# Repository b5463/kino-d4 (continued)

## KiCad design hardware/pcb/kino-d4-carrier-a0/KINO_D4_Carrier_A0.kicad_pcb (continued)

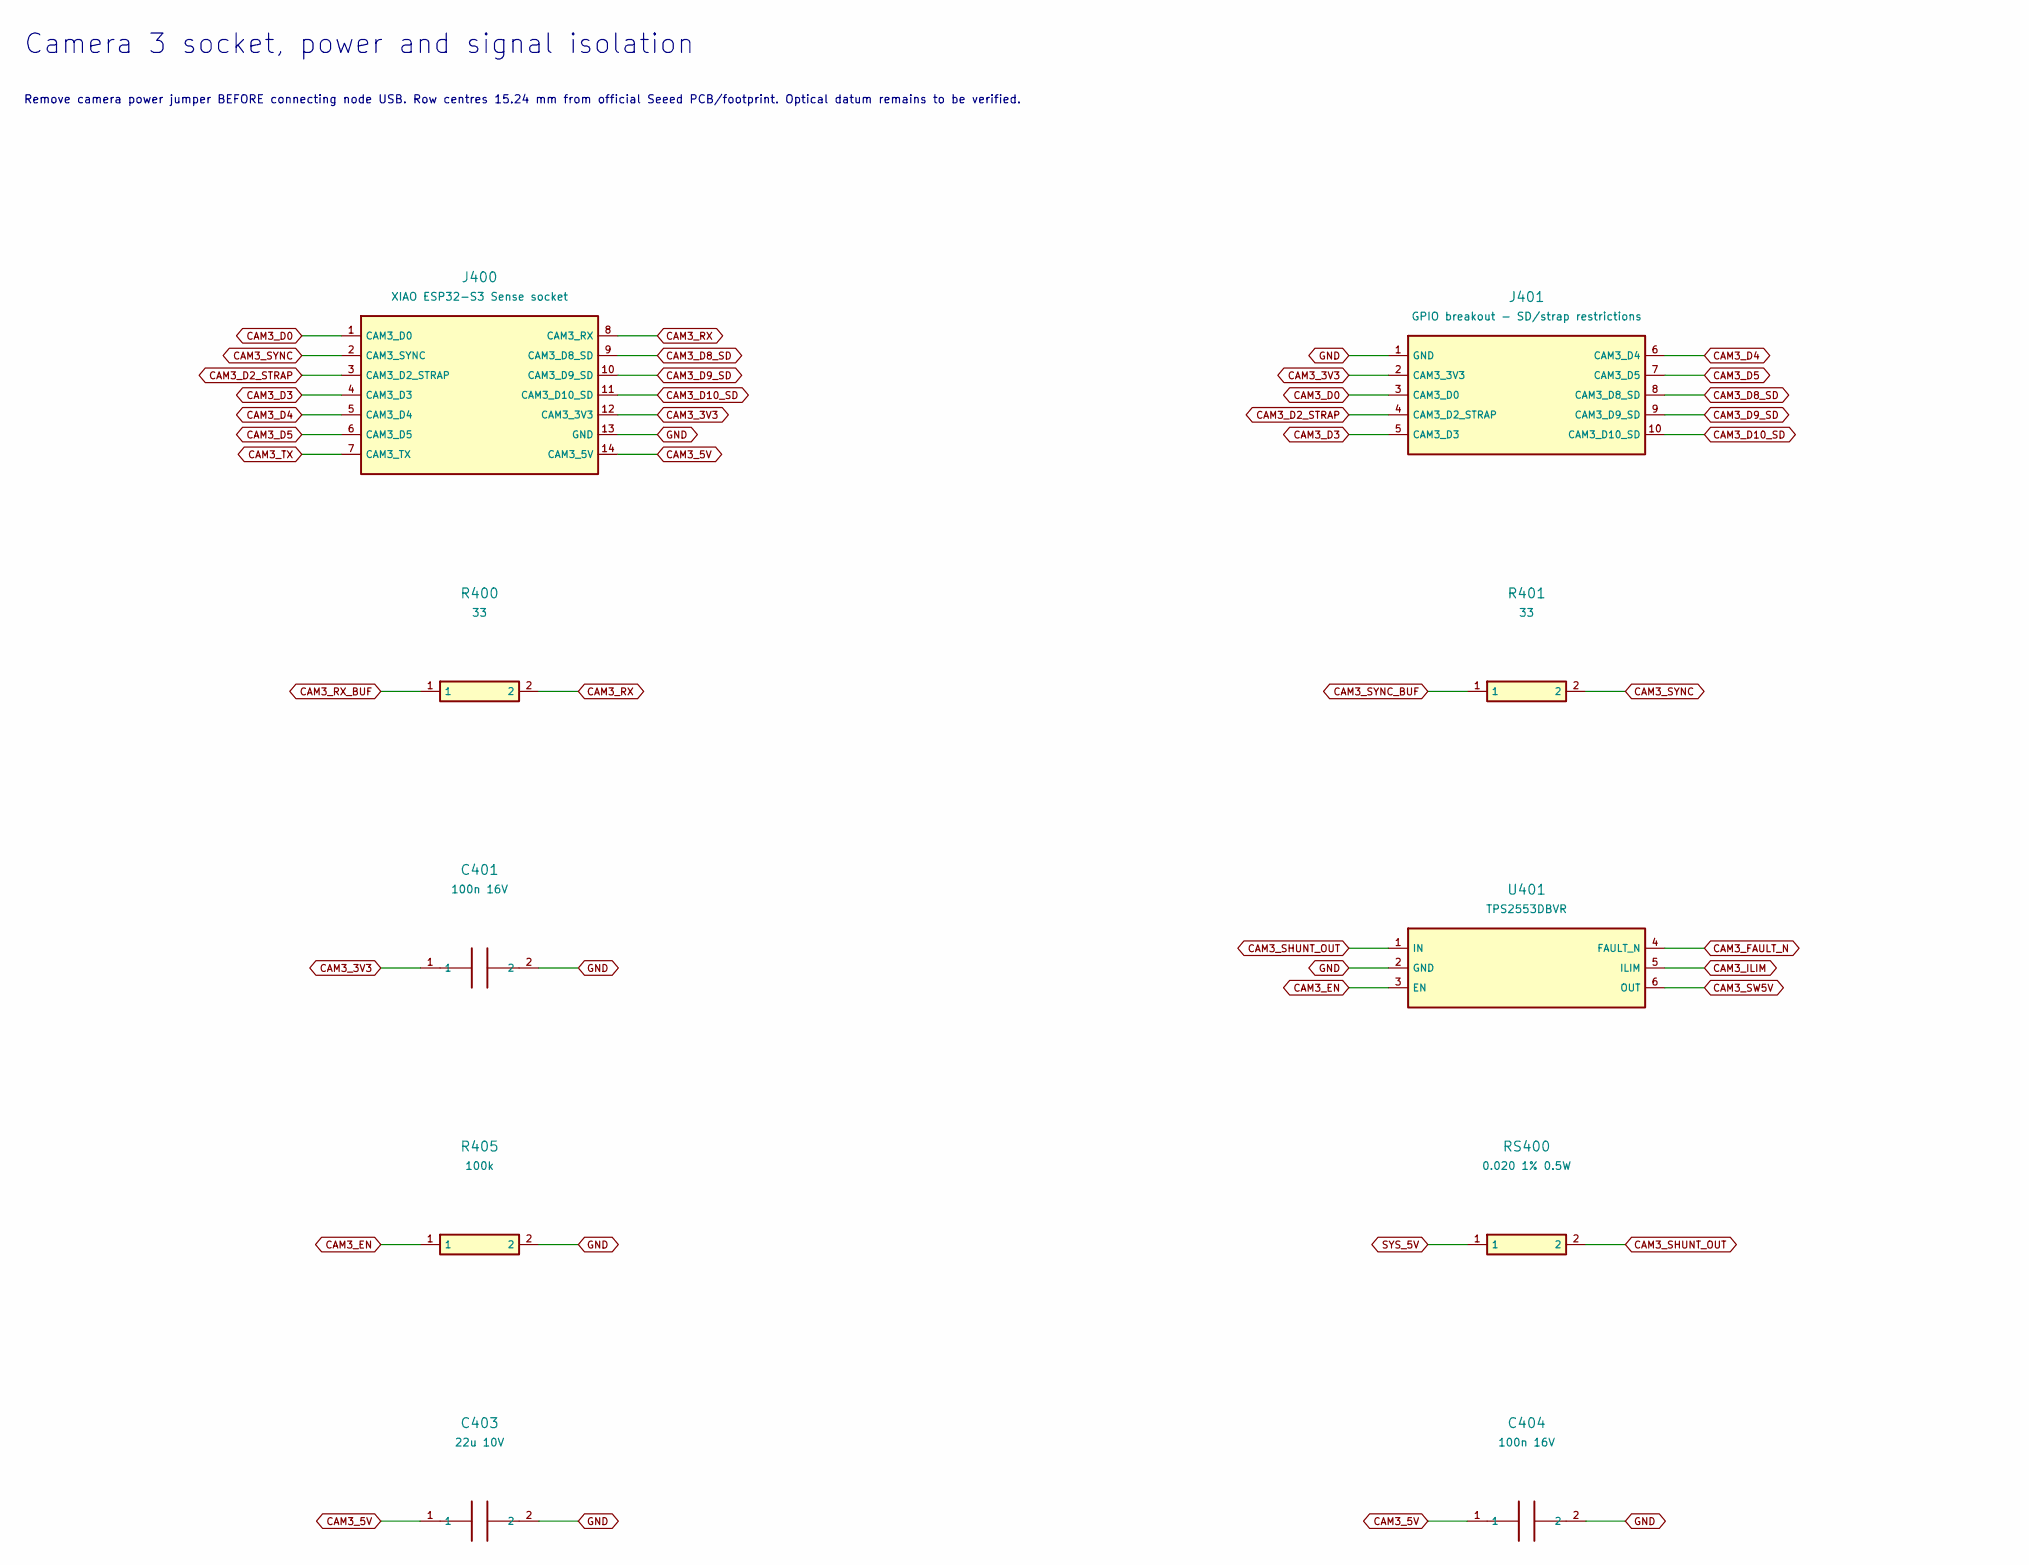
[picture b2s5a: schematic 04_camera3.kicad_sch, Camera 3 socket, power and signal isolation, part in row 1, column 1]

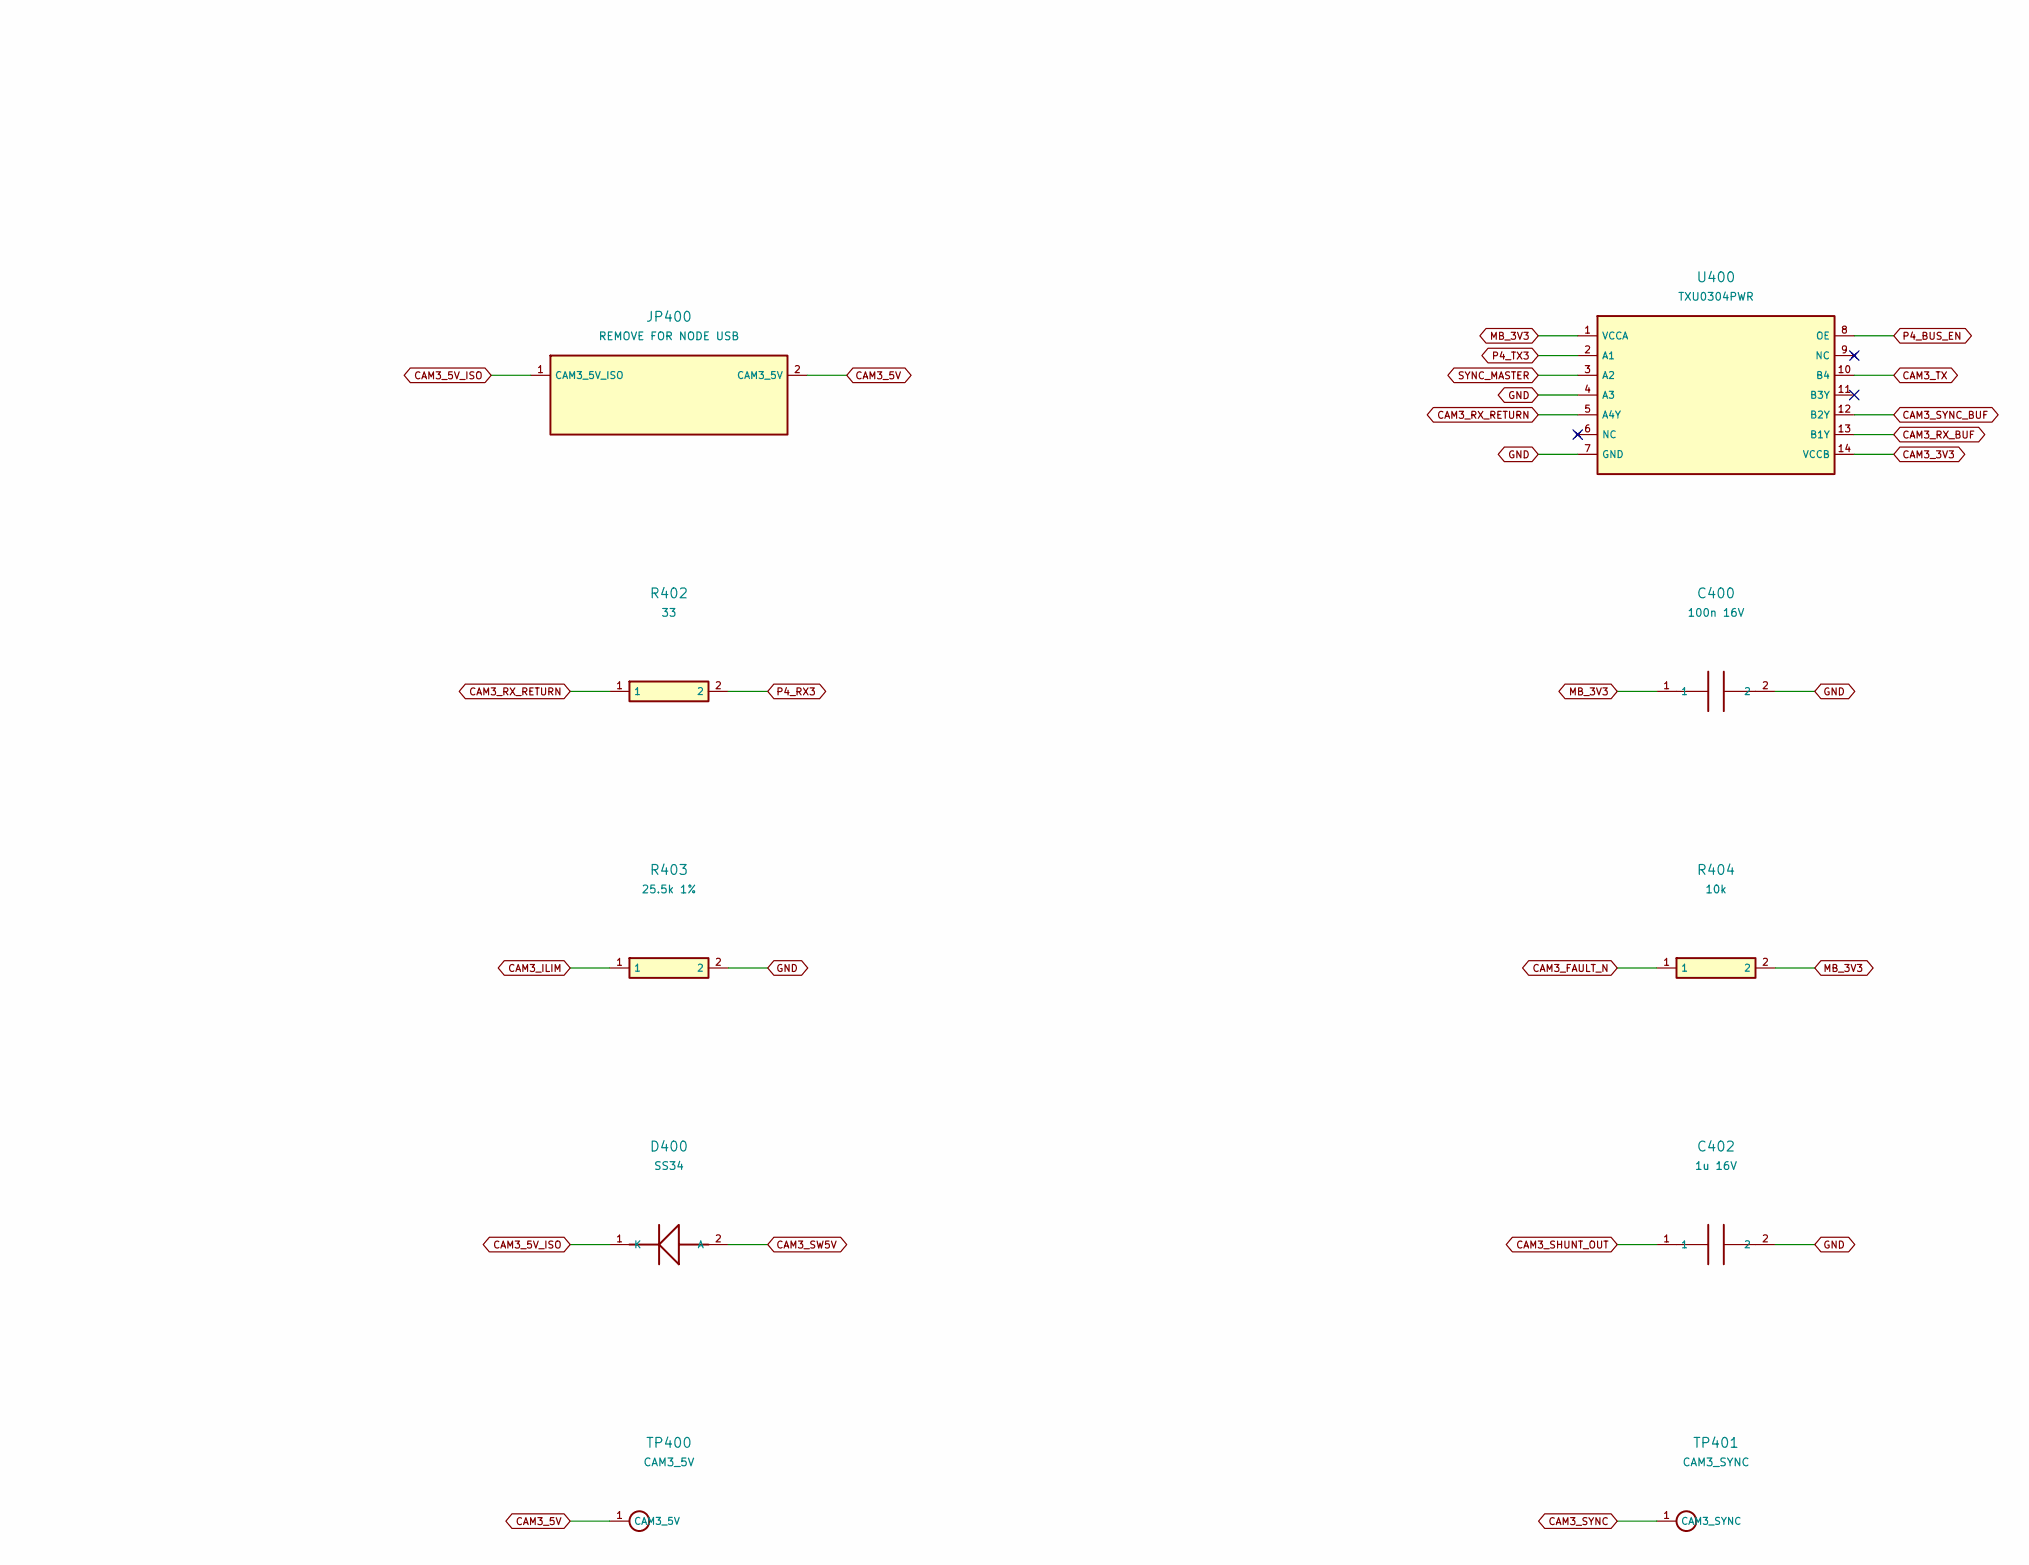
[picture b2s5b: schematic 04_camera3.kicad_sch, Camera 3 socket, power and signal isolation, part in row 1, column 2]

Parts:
C400, C401, C404: 100n 16V; C_0603_1608Metric
C402: 1u 16V; C_0603_1608Metric
C403: 22u 10V; C_0805_2012Metric
D400: SS34; D_SMA
J400: XIAO ESP32-S3 Sense socket; XIAO_Socket_15.24mm
J401: GPIO breakout - SD/strap restrictions; PinHeader_2x05_P2.54mm_Vertical
JP400: REMOVE FOR NODE USB; PinHeader_1x02_P2.54mm_Vertical
R400, R401, R402: 33; R_0603_1608Metric
R403: 25.5k 1%; R_0603_1608Metric
R404: 10k; R_0603_1608Metric
R405: 100k; R_0603_1608Metric
RS400: 0.020 1% 0.5W; R_1206_3216Metric
TP400: CAM3_5V; TestPoint_Pad_D1.5mm
TP401: CAM3_SYNC; TestPoint_Pad_D1.5mm
U400: TXU0304PWR; TSSOP-14_4.4x5mm_P0.65mm
U401: TPS2553DBVR; SOT-23-6

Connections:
CAM3_3V3: C401.1, J400.12 (CAM3_3V3), J401.2 (CAM3_3V3), U400.14 (VCCB)
CAM3_5V: C403.1, C404.1, J400.14 (CAM3_5V), JP400.2 (CAM3_5V), TP400.1
CAM3_5V_ISO: D400.1 (K), JP400.1 (CAM3_5V_ISO)
CAM3_D0: J400.1 (CAM3_D0), J401.3 (CAM3_D0)
CAM3_D2_STRAP: J400.3 (CAM3_D2_STRAP), J401.4 (CAM3_D2_STRAP)
CAM3_D3: J400.4 (CAM3_D3), J401.5 (CAM3_D3)
CAM3_D4: J400.5 (CAM3_D4), J401.6 (CAM3_D4)
CAM3_D5: J400.6 (CAM3_D5), J401.7 (CAM3_D5)
CAM3_D8_SD: J400.9 (CAM3_D8_SD), J401.8 (CAM3_D8_SD)
CAM3_D9_SD: J400.10 (CAM3_D9_SD), J401.9 (CAM3_D9_SD)
CAM3_D10_SD: J400.11 (CAM3_D10_SD), J401.10 (CAM3_D10_SD)
CAM3_EN: R405.1, U401.3 (EN); also elsewhere on the board
CAM3_FAULT_N: R404.1, U401.4 (FAULT_N); also elsewhere on the board
CAM3_ILIM: R403.1, U401.5 (ILIM)
CAM3_RX: J400.8 (CAM3_RX), R400.2
CAM3_RX_BUF: R400.1, U400.13 (B1Y)
CAM3_RX_RETURN: R402.1, U400.5 (A4Y)
CAM3_SHUNT_OUT: C402.1, RS400.2, U401.1 (IN); also elsewhere on the board
CAM3_SW5V: D400.2 (A), U401.6 (OUT)
CAM3_SYNC: J400.2 (CAM3_SYNC), R401.2, TP401.1
CAM3_SYNC_BUF: R401.1, U400.12 (B2Y)
CAM3_TX: J400.7 (CAM3_TX), U400.10 (B4)
MB_3V3: C400.1, R404.2, U400.1 (VCCA); also elsewhere on the board
P4_BUS_EN: U400.8 (OE); also elsewhere on the board
P4_RX3: R402.2; also elsewhere on the board
P4_TX3: U400.2 (A1); also elsewhere on the board
SYNC_MASTER: U400.3 (A2); also elsewhere on the board
SYS_5V: RS400.1; also elsewhere on the board

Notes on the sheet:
Camera 3 socket, power and signal isolation
Remove camera power jumper BEFORE connecting node USB. Row centres 15.24 mm from official Seeed PCB/footprint. Optical datum remains to be verified.

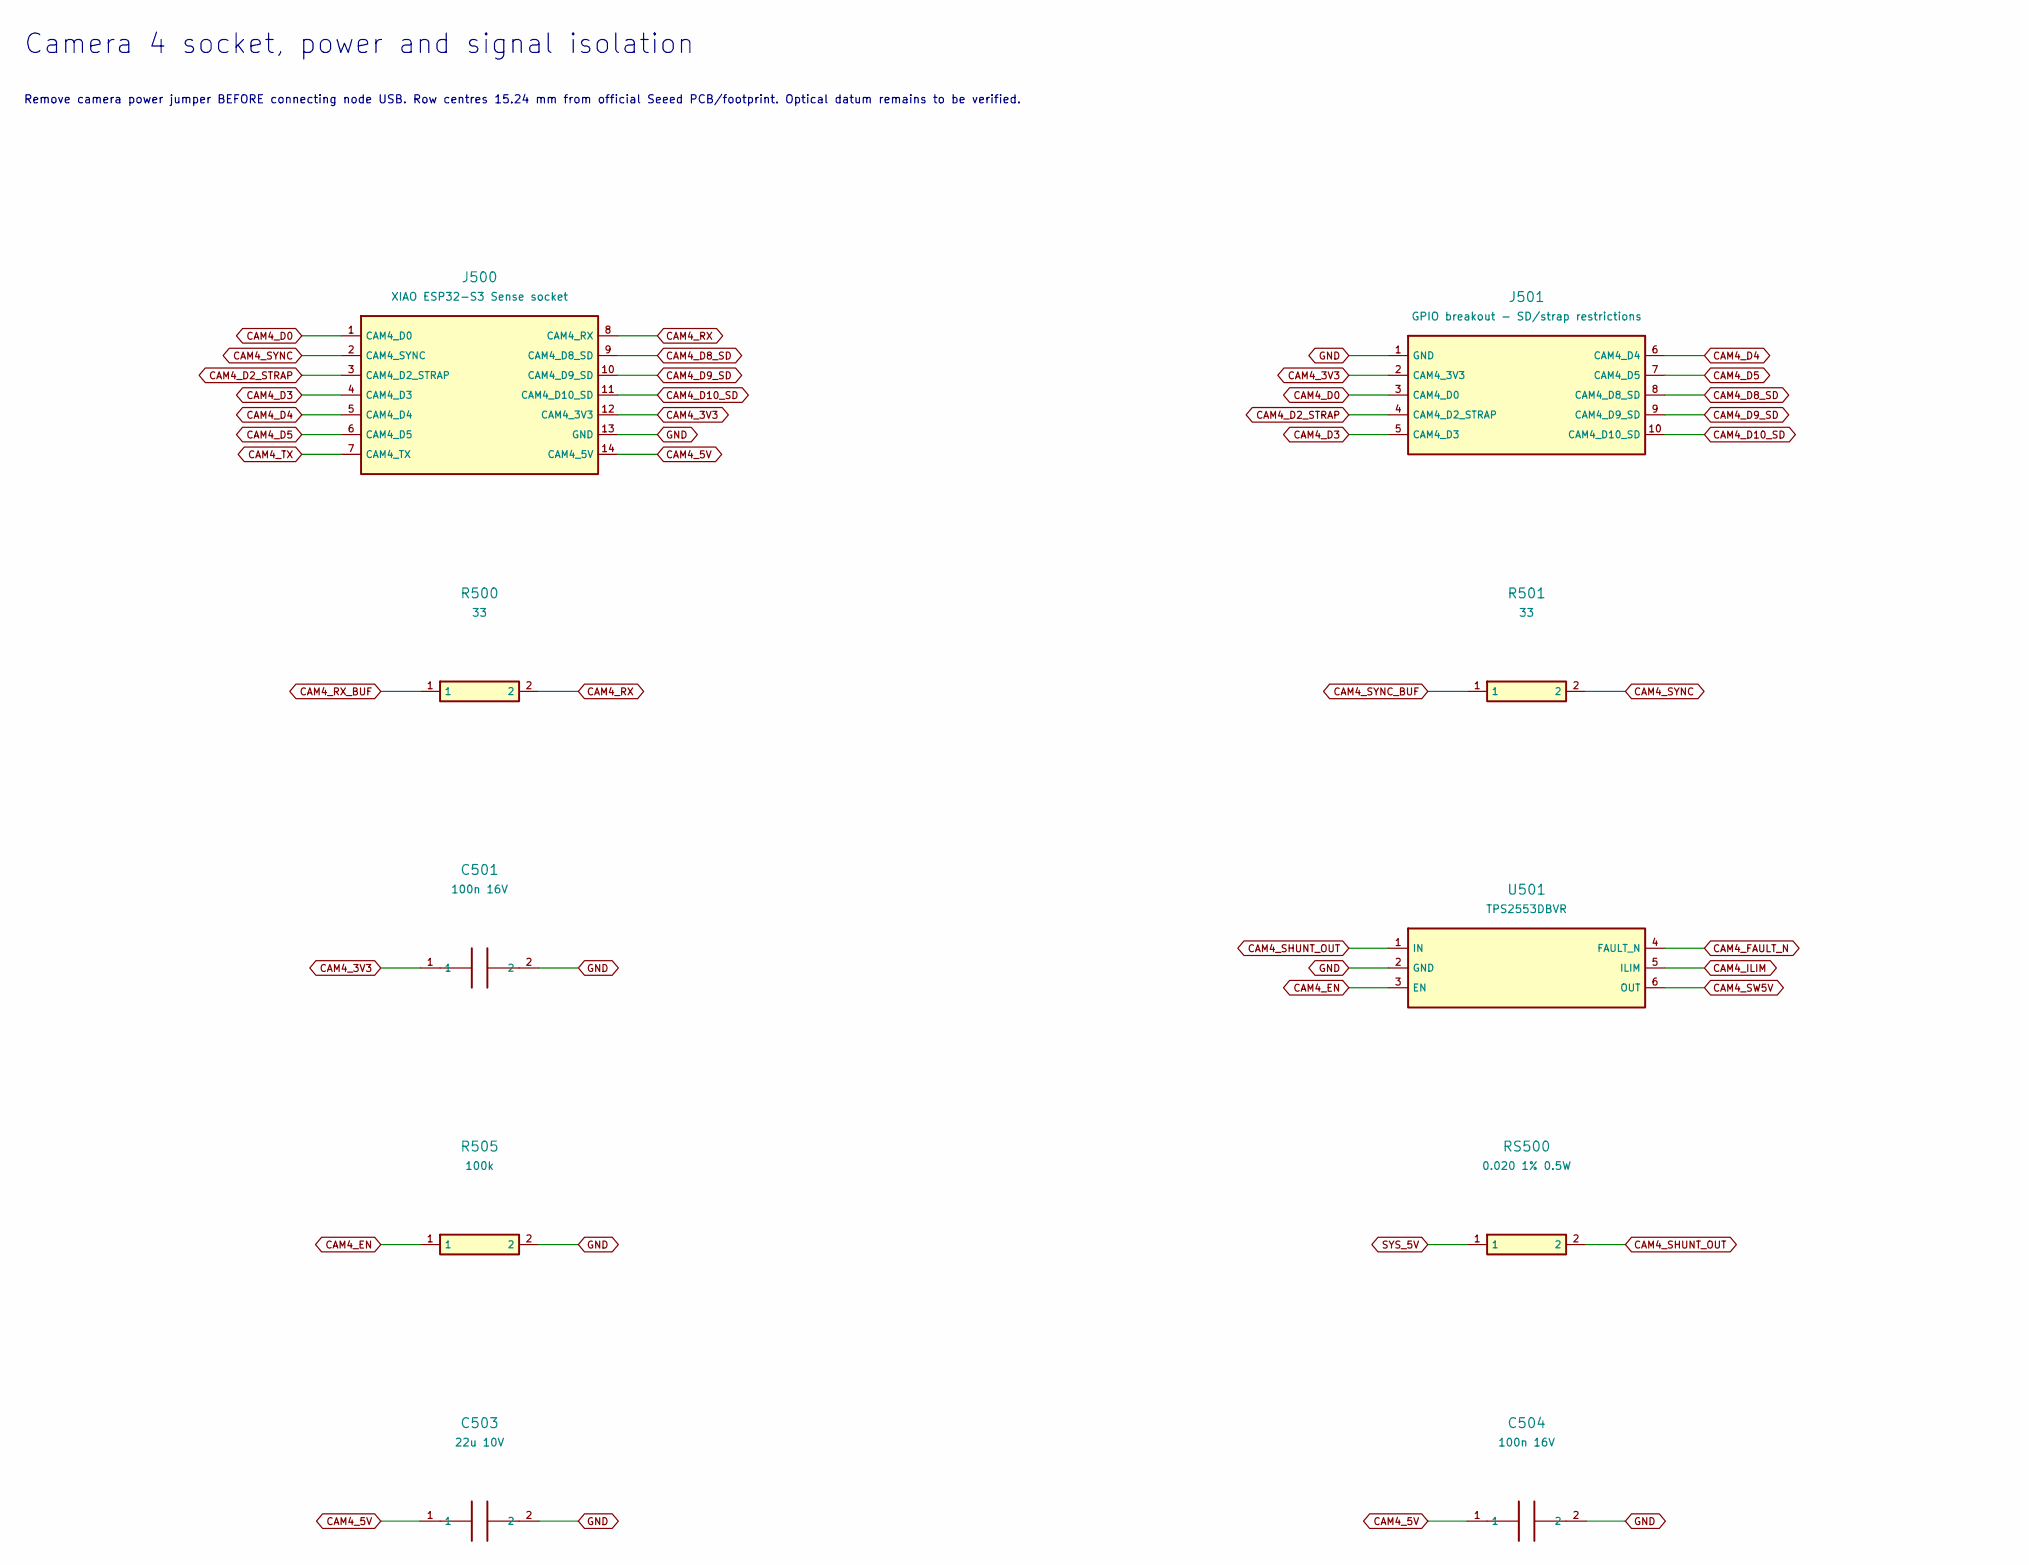
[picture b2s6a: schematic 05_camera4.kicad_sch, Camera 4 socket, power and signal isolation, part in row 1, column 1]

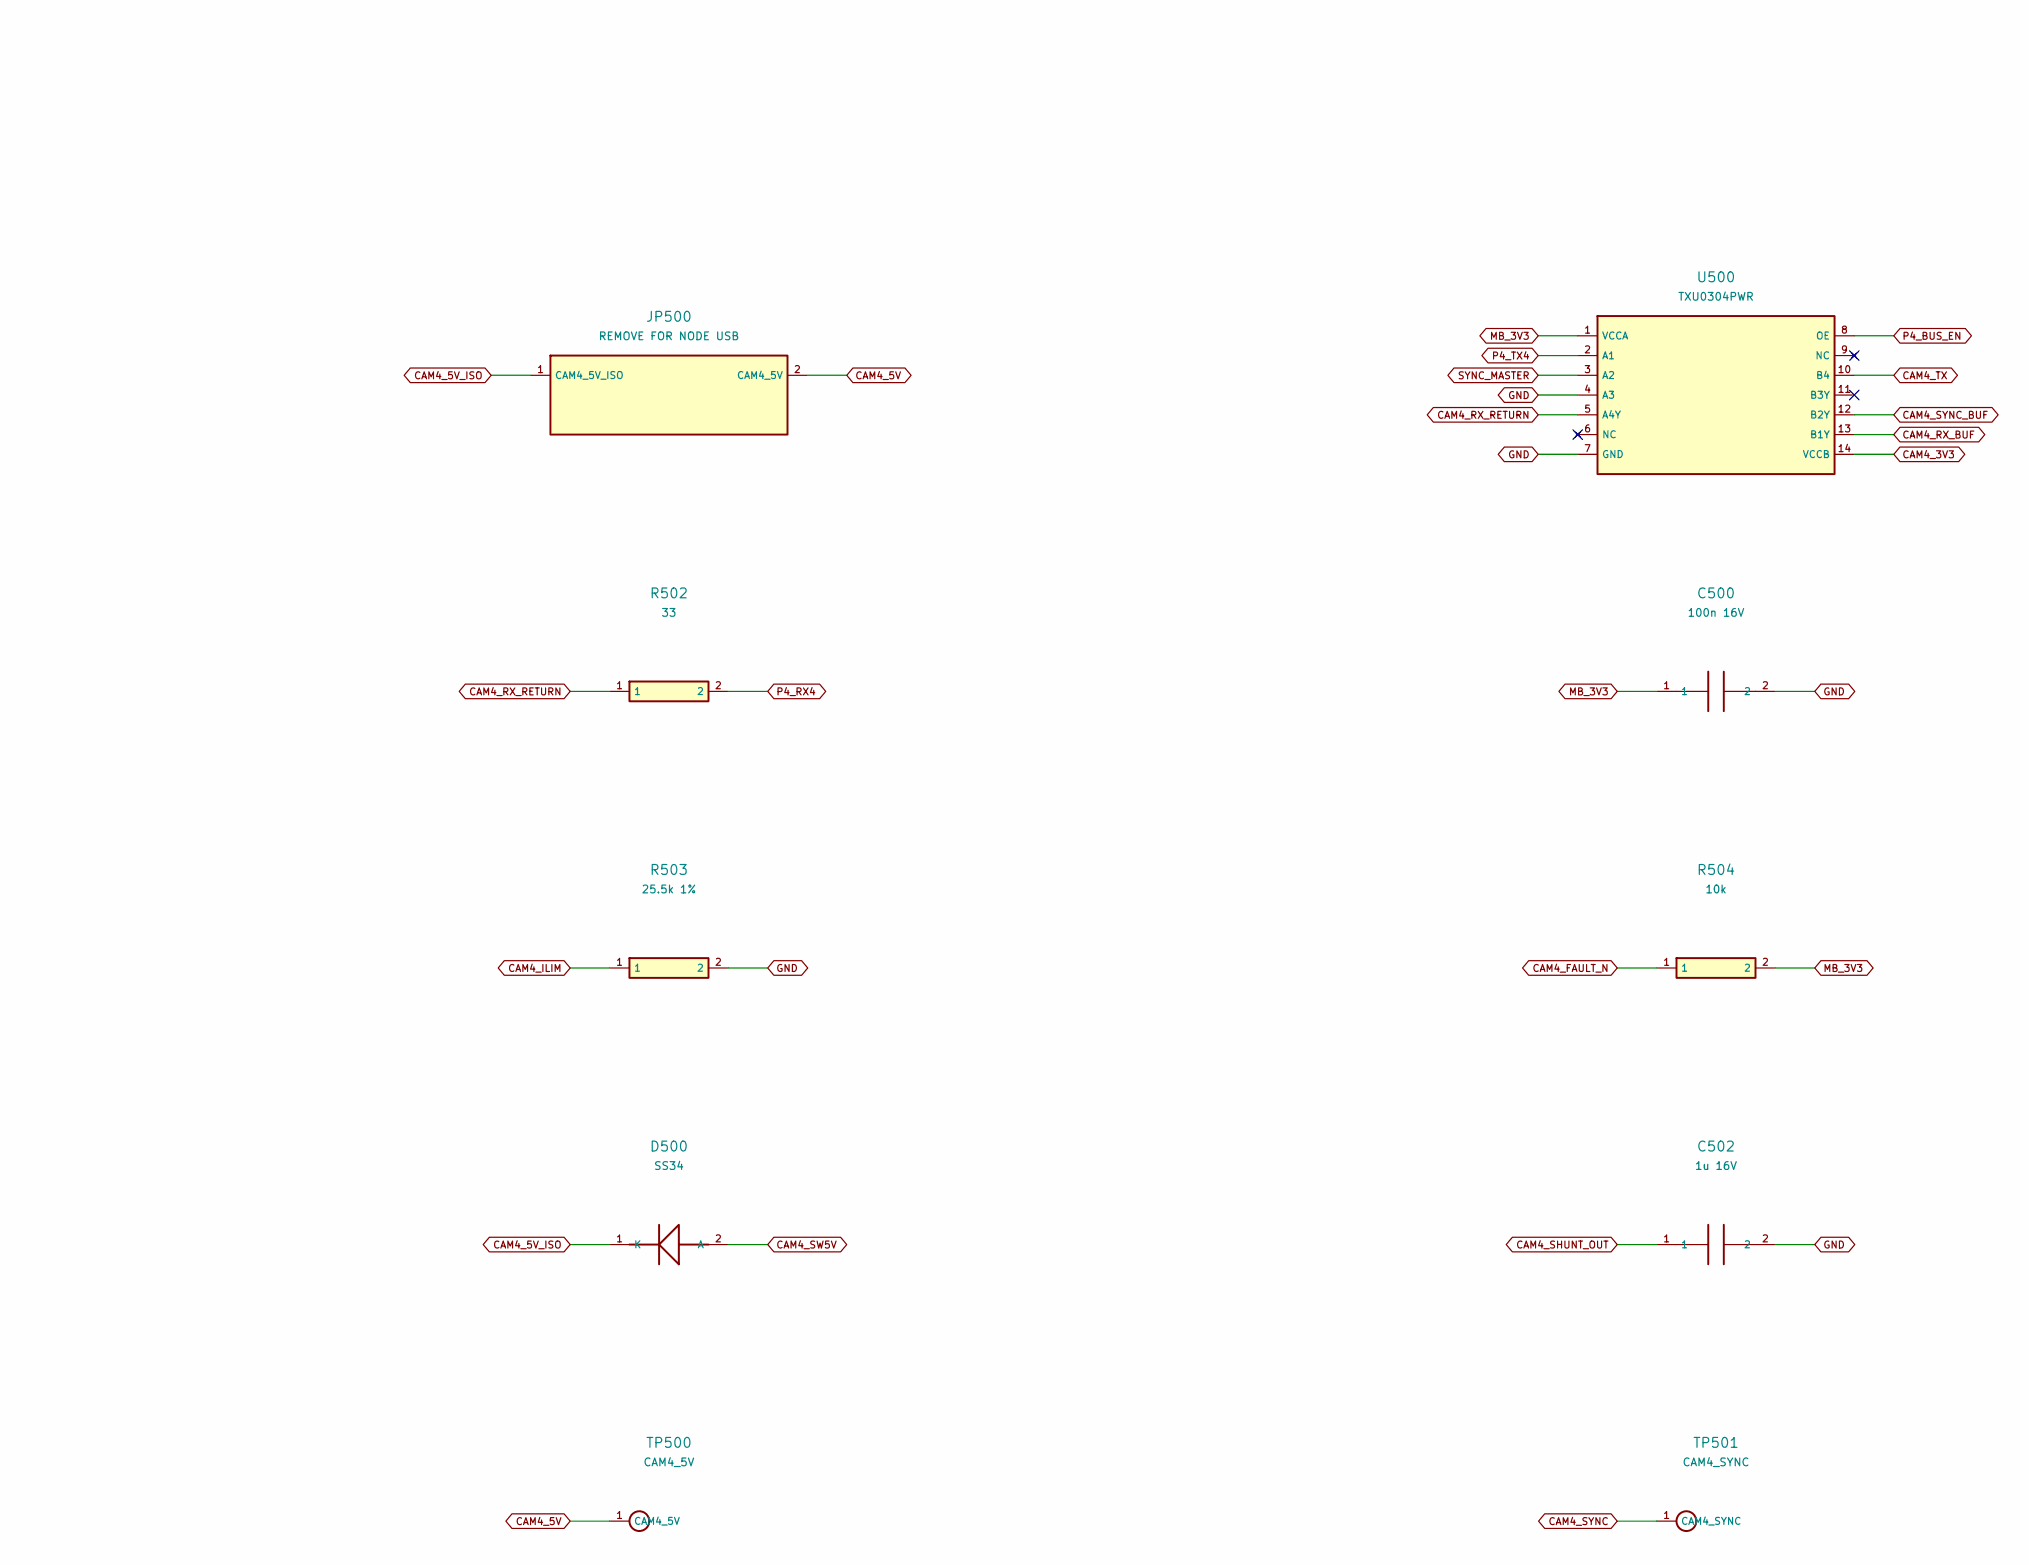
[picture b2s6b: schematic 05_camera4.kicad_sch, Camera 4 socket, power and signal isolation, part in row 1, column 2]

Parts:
C500, C501, C504: 100n 16V; C_0603_1608Metric
C502: 1u 16V; C_0603_1608Metric
C503: 22u 10V; C_0805_2012Metric
D500: SS34; D_SMA
J500: XIAO ESP32-S3 Sense socket; XIAO_Socket_15.24mm
J501: GPIO breakout - SD/strap restrictions; PinHeader_2x05_P2.54mm_Vertical
JP500: REMOVE FOR NODE USB; PinHeader_1x02_P2.54mm_Vertical
R500, R501, R502: 33; R_0603_1608Metric
R503: 25.5k 1%; R_0603_1608Metric
R504: 10k; R_0603_1608Metric
R505: 100k; R_0603_1608Metric
RS500: 0.020 1% 0.5W; R_1206_3216Metric
TP500: CAM4_5V; TestPoint_Pad_D1.5mm
TP501: CAM4_SYNC; TestPoint_Pad_D1.5mm
U500: TXU0304PWR; TSSOP-14_4.4x5mm_P0.65mm
U501: TPS2553DBVR; SOT-23-6

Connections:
CAM4_3V3: C501.1, J500.12 (CAM4_3V3), J501.2 (CAM4_3V3), U500.14 (VCCB)
CAM4_5V: C503.1, C504.1, J500.14 (CAM4_5V), JP500.2 (CAM4_5V), TP500.1
CAM4_5V_ISO: D500.1 (K), JP500.1 (CAM4_5V_ISO)
CAM4_D0: J500.1 (CAM4_D0), J501.3 (CAM4_D0)
CAM4_D2_STRAP: J500.3 (CAM4_D2_STRAP), J501.4 (CAM4_D2_STRAP)
CAM4_D3: J500.4 (CAM4_D3), J501.5 (CAM4_D3)
CAM4_D4: J500.5 (CAM4_D4), J501.6 (CAM4_D4)
CAM4_D5: J500.6 (CAM4_D5), J501.7 (CAM4_D5)
CAM4_D8_SD: J500.9 (CAM4_D8_SD), J501.8 (CAM4_D8_SD)
CAM4_D9_SD: J500.10 (CAM4_D9_SD), J501.9 (CAM4_D9_SD)
CAM4_D10_SD: J500.11 (CAM4_D10_SD), J501.10 (CAM4_D10_SD)
CAM4_EN: R505.1, U501.3 (EN); also elsewhere on the board
CAM4_FAULT_N: R504.1, U501.4 (FAULT_N); also elsewhere on the board
CAM4_ILIM: R503.1, U501.5 (ILIM)
CAM4_RX: J500.8 (CAM4_RX), R500.2
CAM4_RX_BUF: R500.1, U500.13 (B1Y)
CAM4_RX_RETURN: R502.1, U500.5 (A4Y)
CAM4_SHUNT_OUT: C502.1, RS500.2, U501.1 (IN); also elsewhere on the board
CAM4_SW5V: D500.2 (A), U501.6 (OUT)
CAM4_SYNC: J500.2 (CAM4_SYNC), R501.2, TP501.1
CAM4_SYNC_BUF: R501.1, U500.12 (B2Y)
CAM4_TX: J500.7 (CAM4_TX), U500.10 (B4)
MB_3V3: C500.1, R504.2, U500.1 (VCCA); also elsewhere on the board
P4_BUS_EN: U500.8 (OE); also elsewhere on the board
P4_RX4: R502.2; also elsewhere on the board
P4_TX4: U500.2 (A1); also elsewhere on the board
SYNC_MASTER: U500.3 (A2); also elsewhere on the board
SYS_5V: RS500.1; also elsewhere on the board

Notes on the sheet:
Camera 4 socket, power and signal isolation
Remove camera power jumper BEFORE connecting node USB. Row centres 15.24 mm from official Seeed PCB/footprint. Optical datum remains to be verified.

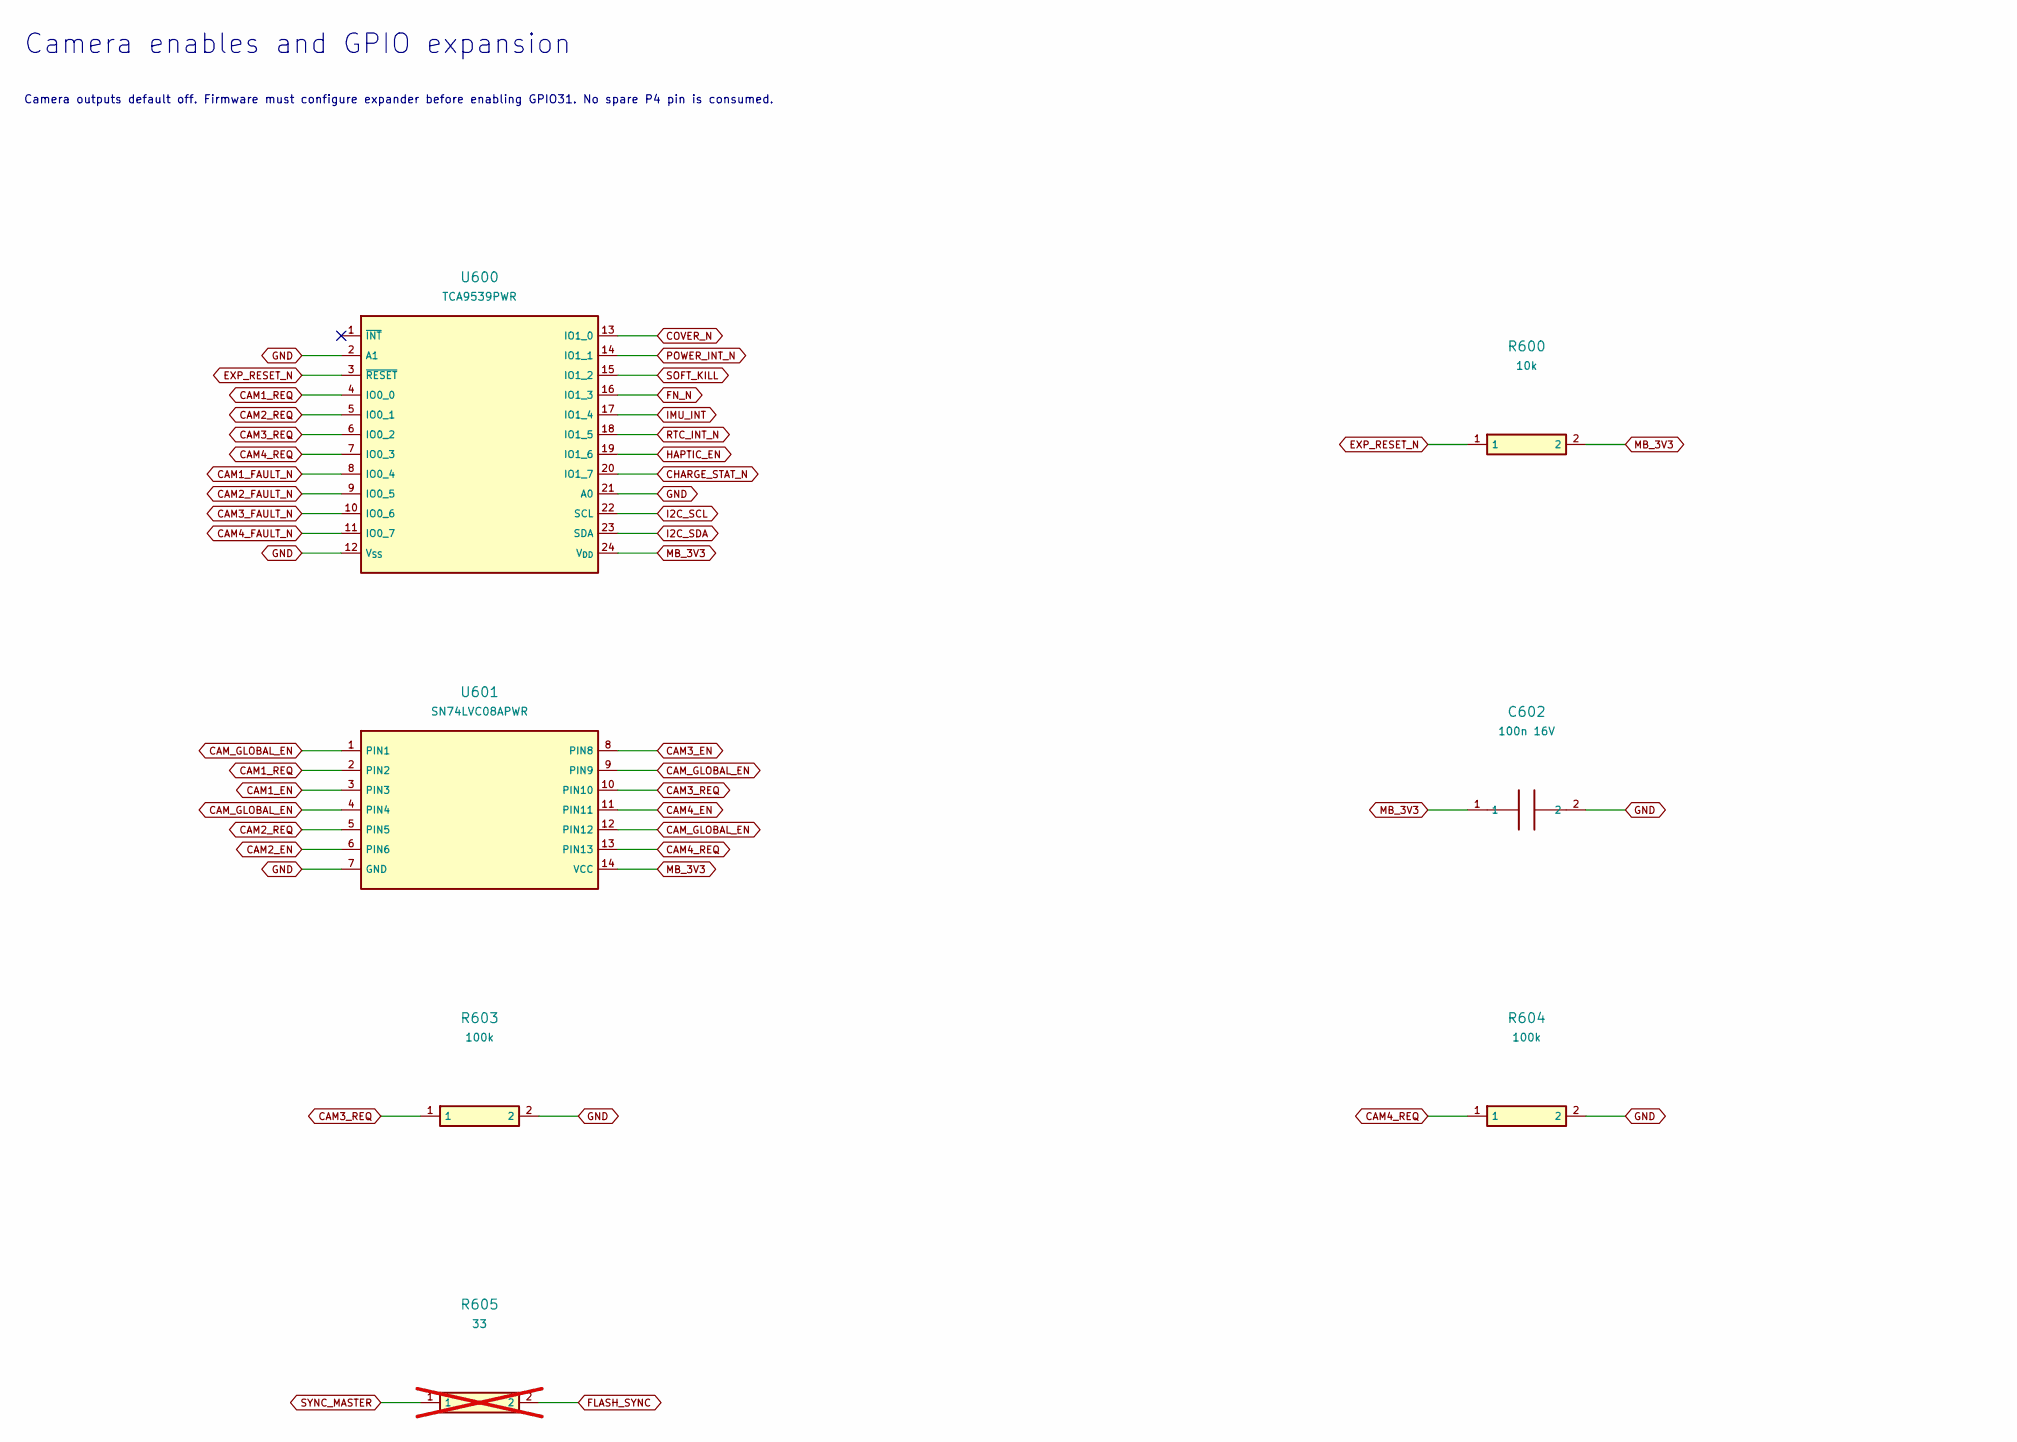
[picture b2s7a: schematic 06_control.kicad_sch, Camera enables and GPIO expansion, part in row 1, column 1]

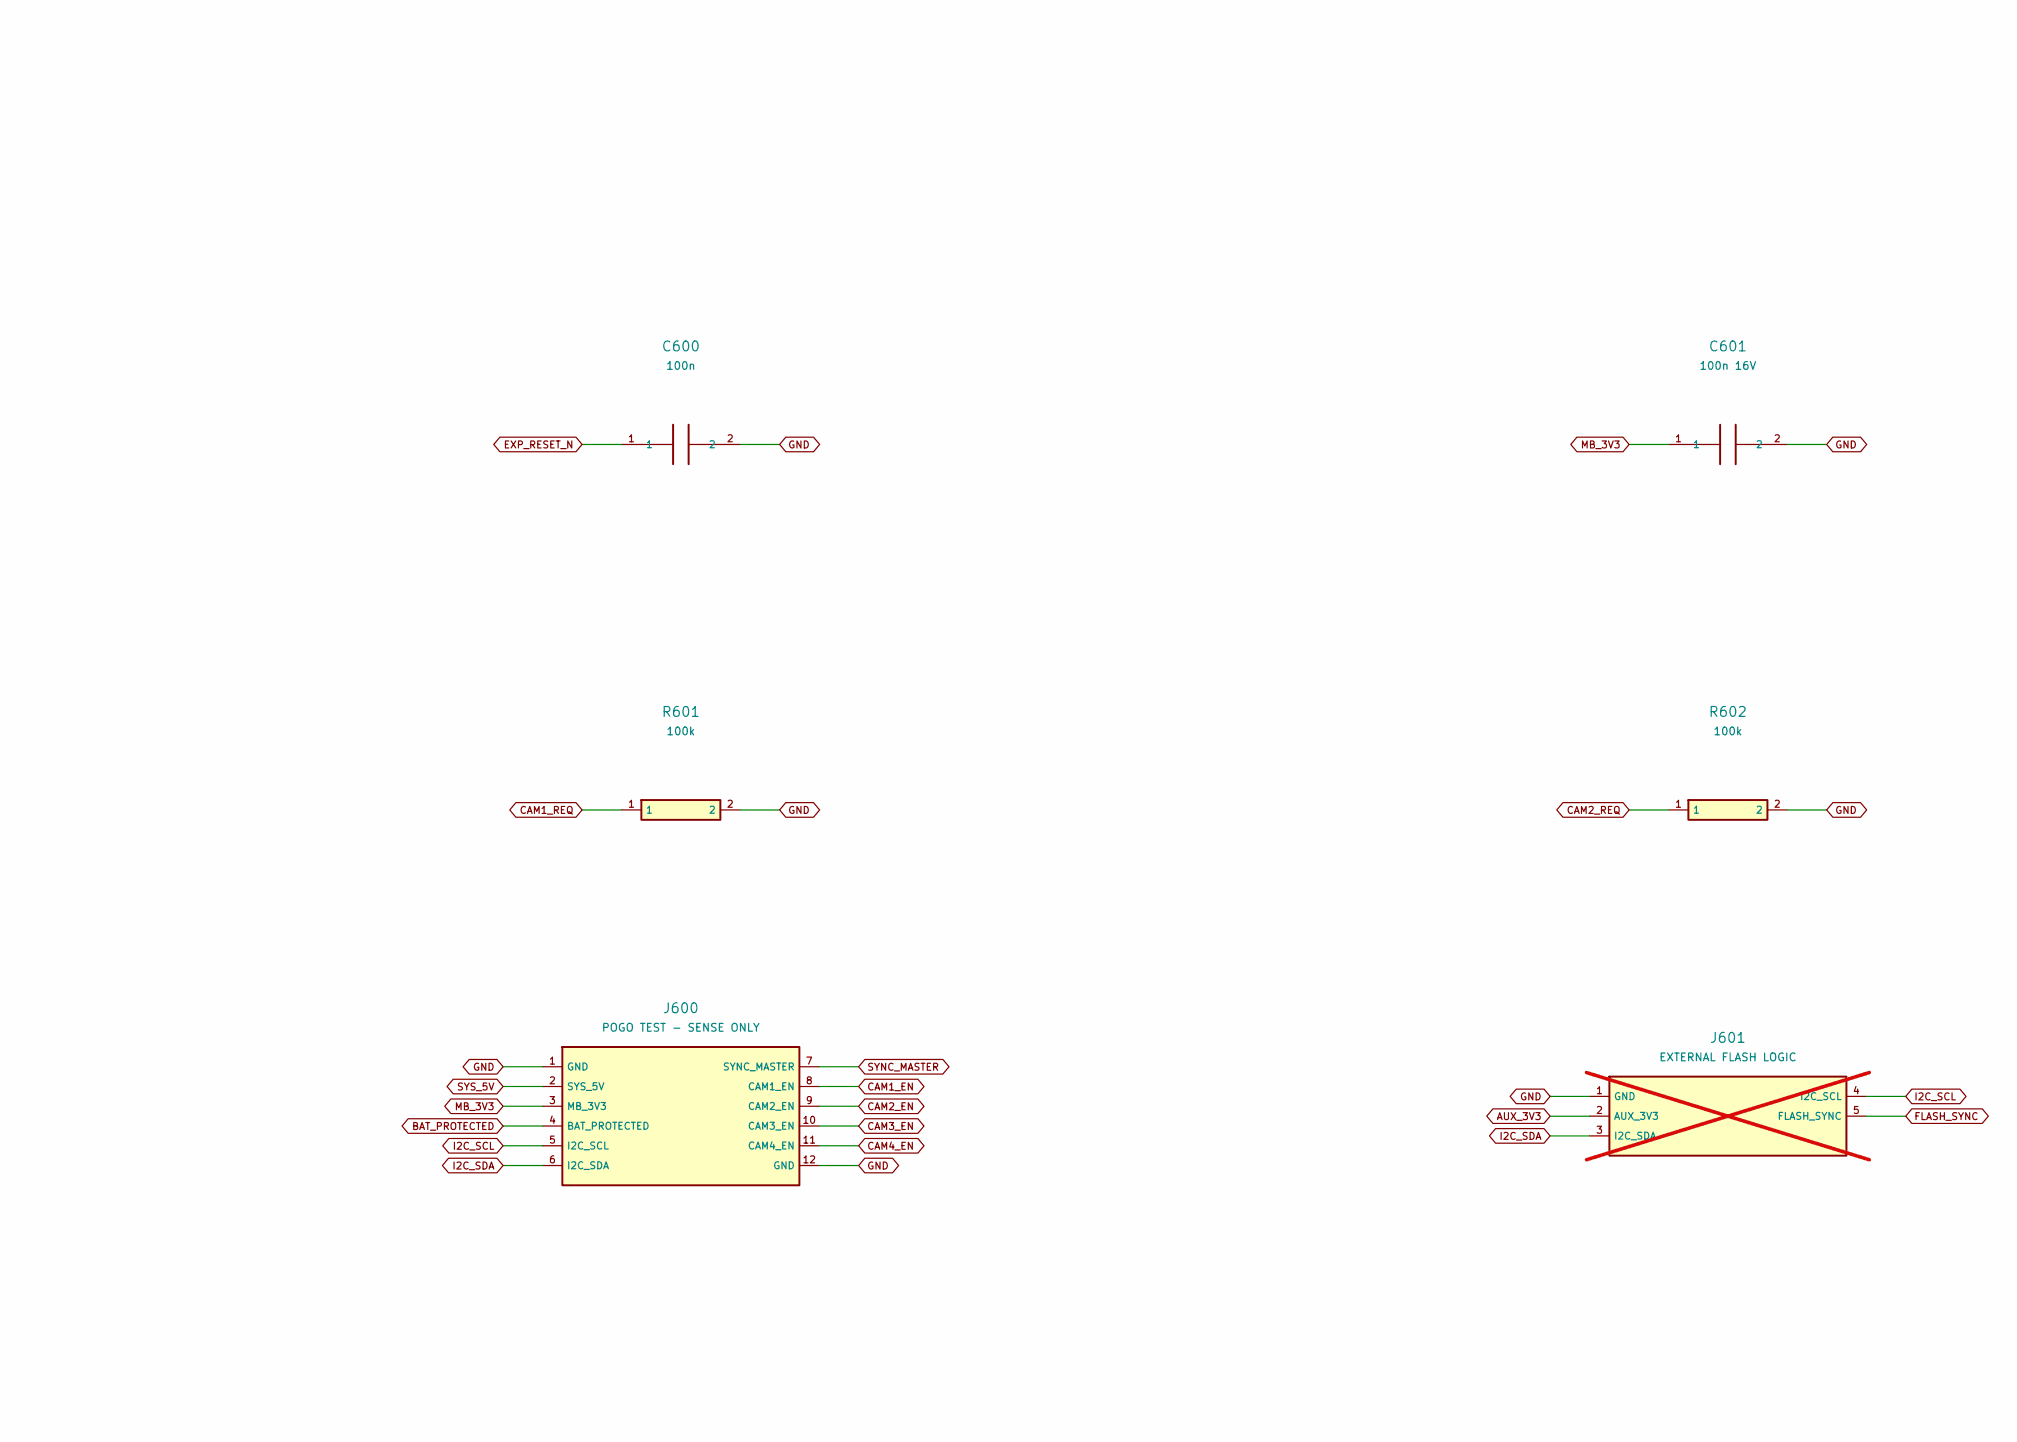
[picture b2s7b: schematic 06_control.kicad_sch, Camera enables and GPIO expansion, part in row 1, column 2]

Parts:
C600: 100n; C_0603_1608Metric
C601, C602: 100n 16V; C_0603_1608Metric
J600: POGO TEST - SENSE ONLY; Pogo_12_Asymmetric
J601: EXTERNAL FLASH LOGIC; JST_GH_BM05B-GHS-TBT_1x05-1MP_P1.25mm_Vertical; not fitted
R600: 10k; R_0603_1608Metric
R601, R602, R603, R604: 100k; R_0603_1608Metric
R605: 33; R_0603_1608Metric; not fitted
U600: TCA9539PWR; TSSOP-24_4.4x7.8mm_P0.65mm
U601: SN74LVC08APWR; TSSOP-14_4.4x5mm_P0.65mm

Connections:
CAM1_EN: J600.8 (CAM1_EN), U601.3 (PIN3); also elsewhere on the board
CAM1_FAULT_N: U600.8 (IO0_4); also elsewhere on the board
CAM1_REQ: R601.1, U600.4 (IO0_0), U601.2 (PIN2)
CAM2_EN: J600.9 (CAM2_EN), U601.6 (PIN6); also elsewhere on the board
CAM2_FAULT_N: U600.9 (IO0_5); also elsewhere on the board
CAM2_REQ: R602.1, U600.5 (IO0_1), U601.5 (PIN5)
CAM3_EN: J600.10 (CAM3_EN), U601.8 (PIN8); also elsewhere on the board
CAM3_FAULT_N: U600.10 (IO0_6); also elsewhere on the board
CAM3_REQ: R603.1, U600.6 (IO0_2), U601.10 (PIN10)
CAM4_EN: J600.11 (CAM4_EN), U601.11 (PIN11); also elsewhere on the board
CAM4_FAULT_N: U600.11 (IO0_7); also elsewhere on the board
CAM4_REQ: R604.1, U600.7 (IO0_3), U601.13 (PIN13)
CAM_GLOBAL_EN: U601.1 (PIN1), U601.4 (PIN4), U601.9 (PIN9), U601.12 (PIN12); also elsewhere on the board
CHARGE_ARM: U600.20 (IO1_7); also elsewhere on the board
COVER_N: U600.13 (IO1_0); also elsewhere on the board
EXP_RESET_N: C600.1, R600.1, U600.3 (~RESET)
FN_N: U600.16 (IO1_3); also elsewhere on the board
HAPTIC_EN: U600.19 (IO1_6); also elsewhere on the board
I2C_SCL: J600.5 (I2C_SCL), J601.4 (I2C_SCL), U600.22 (SCL); also elsewhere on the board
I2C_SDA: J600.6 (I2C_SDA), J601.3 (I2C_SDA), U600.23 (SDA); also elsewhere on the board
IMU_INT: U600.17 (IO1_4); also elsewhere on the board
MB_3V3: C601.1, C602.1, J600.3 (MB_3V3), R600.2, U600.24 (V_{DD}), U601.14 (VCC); also elsewhere on the board
unnamed: J600.7 (SYNC_MASTER), R605.1
unnamed: J601.5 (FLASH_SYNC), R605.2
POWER_INT_N: U600.14 (IO1_1); also elsewhere on the board
RTC_INT_N: U600.18 (IO1_5); also elsewhere on the board
SOFT_KILL: U600.15 (IO1_2); also elsewhere on the board

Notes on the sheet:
Camera enables and GPIO expansion
Camera outputs default off. Firmware must configure expander before enabling GPIO31. No spare P4 pin is consumed.
